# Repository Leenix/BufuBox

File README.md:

# BufuBox
A comical attempt at making a Peltier fridge out of a crappy $5 foam esky.

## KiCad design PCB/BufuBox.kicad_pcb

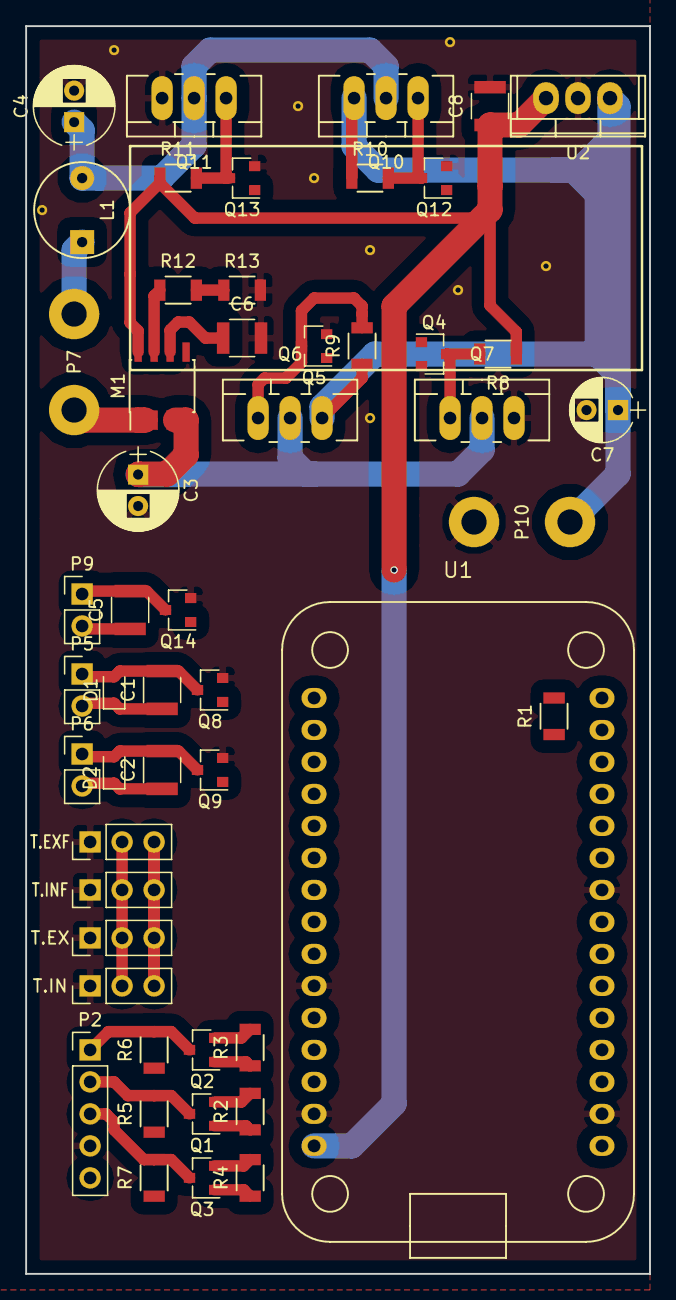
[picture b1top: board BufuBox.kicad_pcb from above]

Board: 2 copper layers, 49.5 x 99.1 mm, 51 parts (0 on the bottom side), 32 nets.

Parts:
C1, C2, C5, C6: 10uF; C_1210
C3, C4: 100uF; CP_Radial_D6.3mm_P2.50mm
C7: 0.33uF; CP_Radial_D5.0mm_P2.50mm
C8: 100nF; C_1210
D1, D2: 1N4818; D_SOD-323
L1: 100uH; INDUCTOR_V
M1: ACS712; SOIC-8_3.9x4.9mm_Pitch1.27mm
P2: Display; Pin_Header_Straight_1x05_Pitch2.54mm
P5: Fan-internal; Pin_Header_Straight_1x02_Pitch2.54mm
P6: Fan-external; Pin_Header_Straight_1x02_Pitch2.54mm
P7: Peltier; WireConnection_2.00mmDrill
P9: LED; Pin_Header_Straight_1x02_Pitch2.54mm
P10: Power; WireConnection_2.00mmDrill
Q1, Q2, Q3, Q4, Q5, Q8, Q9, Q12, Q13, Q14: AO3402; SOT-23
Q6, Q10: FQP27P06; TO-220_Neutral123_Vertical_LargePads
Q7, Q11: FQP30N06L; TO-220_Neutral123_Vertical_LargePads
R1, R2, R3, R4, R5, R6, R7, R8, R9, R10, R11: 4K7; R_1206
R12: 47K; R_1206
R13: 91K; R_1206
T.EX: t-external; Pin_Header_Straight_1x03_Pitch2.54mm
T.EXF: t-fin-external; Pin_Header_Straight_1x03_Pitch2.54mm
T.IN: t-internal; Pin_Header_Straight_1x03_Pitch2.54mm
T.INF: t-fin-internal; Pin_Header_Straight_1x03_Pitch2.54mm
U1: NodeMCUv2; nodemcuv2
U2: LM7805; TO-220

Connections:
+3V3: Q1.1, Q2.1, Q3.1, R1.1, R2.1, R3.1, R4.1, T.EX.3, T.EXF.3, T.IN.3, T.INF.3, U1.3V3
+5V: C8.1, M1.8, P2.5, R5.1, R6.1, R7.1, R8.1, R11.1, U1.Vin, U2.3
+12V: C1.1, C2.1, C5.1, C7.1, D1.1, D2.1, P5.2, P6.2, P9.2, P10.2, Q6.3, Q10.3, R9.1, R10.1, U2.1
GND: C3.2, C4.2, C6.2, C7.2, C8.2, M1.5, P2.4, P10.1, Q4.2, Q5.2, Q7.3, Q8.2, Q9.2, Q11.3, Q12.2, Q13.2, Q14.2, R13.2, T.EX.1, T.EXF.1, T.IN.1, T.INF.1, U1.GND, U2.2
unnamed: C1.2, D1.2, P5.1, Q8.3
unnamed: C2.2, D2.2, P6.1, Q9.3
unnamed: C4.1, L1.2, Q10.2, Q11.2
unnamed: C5.2, P9.1, Q14.3
unnamed: C6.1, M1.6
unnamed: M1.7, R12.1
unnamed: Q4.3, Q7.1, R8.2
unnamed: Q5.3, Q6.1, R9.2
unnamed: Q10.1, Q12.3, R10.2
unnamed: Q11.1, Q13.3, R11.2
current-sense: R12.2, R13.1, U1.A0
display-clock: Q2.2, R3.2, U1.D4
display-clock-hi: P2.1, Q2.3, R6.2
display-cs: Q1.2, R2.2, U1.D3
display-cs-hi: P2.2, Q1.3, R5.2
display-data: Q3.2, R4.2, U1.D5
display-data-hi: P2.3, Q3.3, R7.2
fan-external: Q9.1, U1.D2
fan-internal: Q8.1, U1.D1
led-control: Q14.1, U1.D10
peltier-left: C3.1, M1.3, M1.4, Q6.2, Q7.2
peltier-left+: M1.1, M1.2, P7.1
peltier-left-A: Q5.1, U1.D6
peltier-left-B: Q4.1, U1.D8
peltier-right: L1.1, P7.2
peltier-right-A: Q12.1, U1.D7
peltier-right-B: Q13.1, U1.D9
temperature: R1.2, T.EX.2, T.EXF.2, T.IN.2, T.INF.2, U1.D0

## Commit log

2019-03-03 Added PCB, I guess (old)
